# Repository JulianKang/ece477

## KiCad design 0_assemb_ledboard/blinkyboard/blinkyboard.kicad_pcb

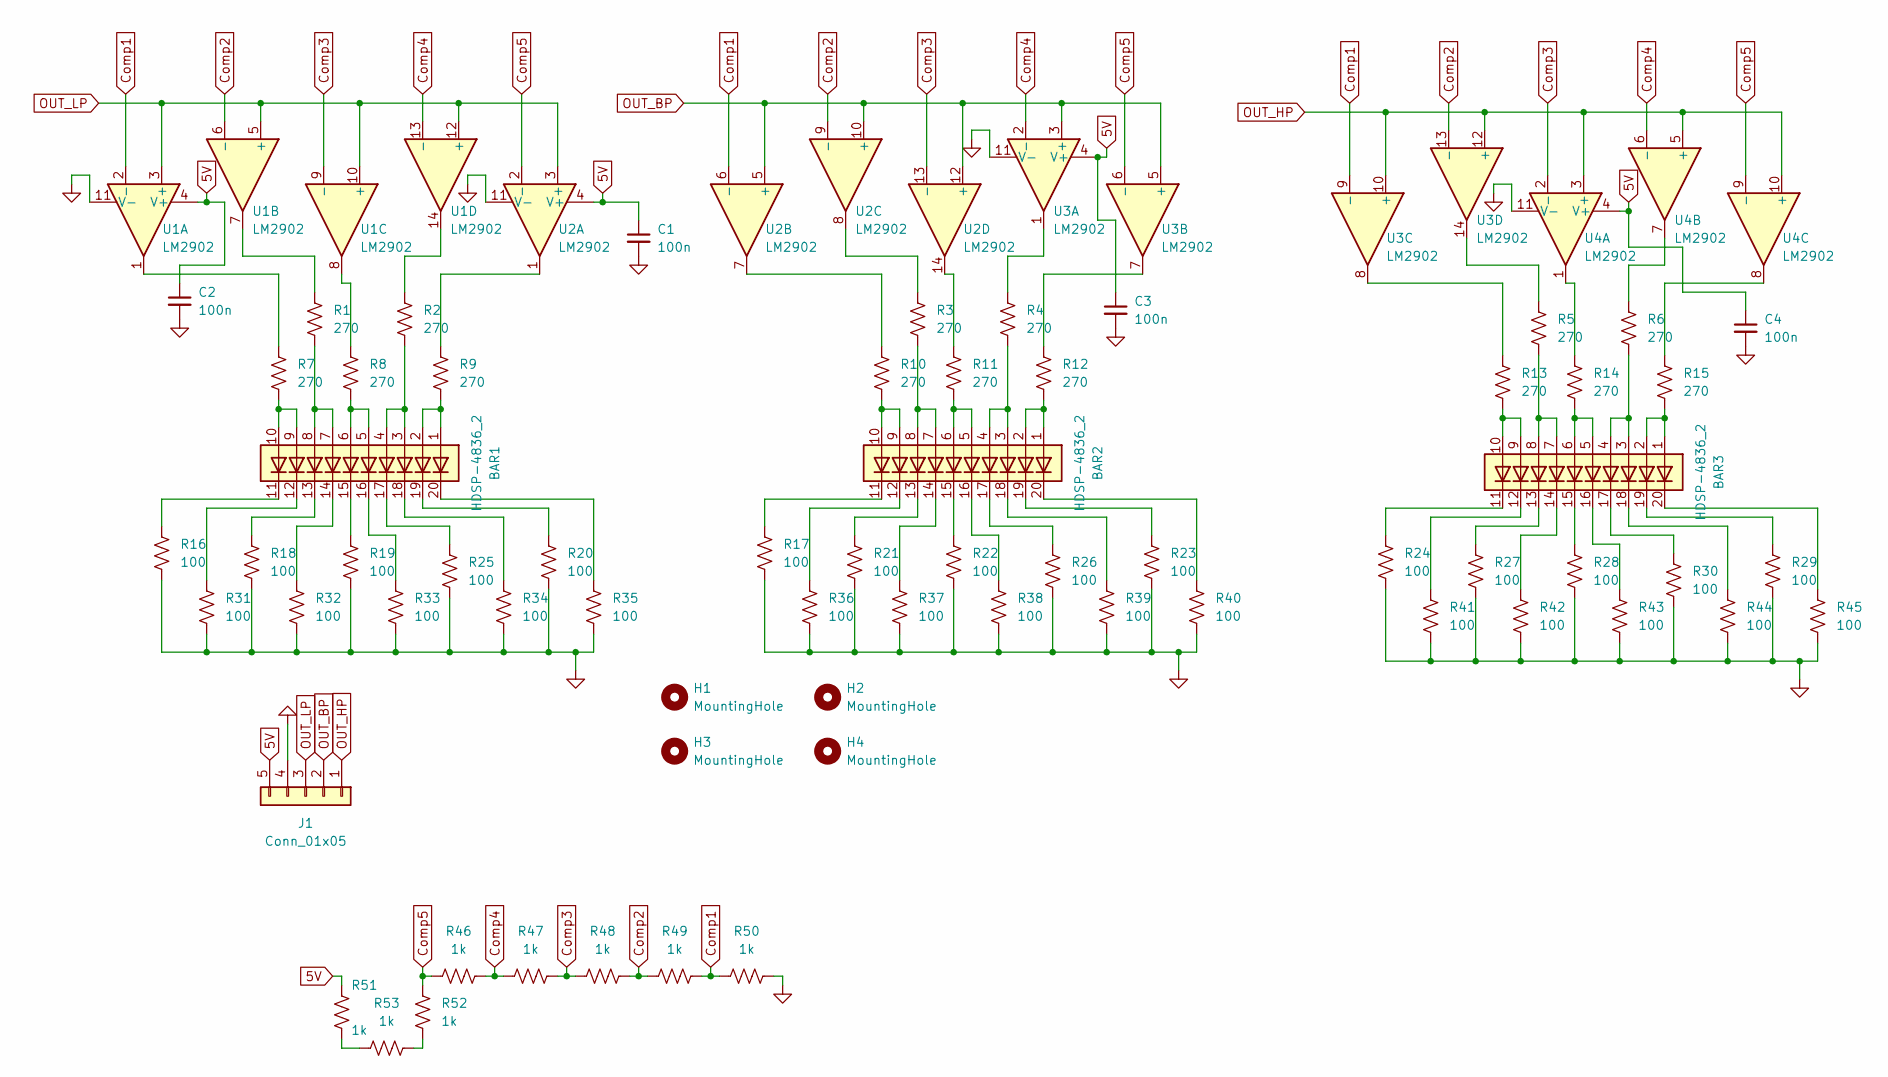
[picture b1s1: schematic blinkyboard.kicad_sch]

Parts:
BAR1, BAR2, BAR3: HDSP-4836_2; HDSP-4836
C1, C2, C3, C4: 100n; C_0805_2012Metric
H1, H2, H3, H4: MountingHole; MountingHole_3.2mm_M3_DIN965
J1: Conn_01x05; PinHeader_1x05_P2.54mm_Vertical
R1, R2, R3, R4, R5, R6, R7, R8, R9, R10, R11, R12, R13, R14, R15: 270; R_0805_2012Metric_Pad1.20x1.40mm_HandSolder
R16, R17, R18, R19, R20, R21, R22, R23, R24, R25, R26, R27, R28, R29, R30, R31, R32, R33, R34, R35, R36, R37, R38, R39, R40, R41, R42, R43, R44, R45: 100; R_0805_2012Metric_Pad1.20x1.40mm_HandSolder
R46, R47, R48, R49, R50, R51, R52, R53: 1k; R_0805_2012Metric_Pad1.20x1.40mm_HandSolder
U1, U2, U3, U4: LM2902; DIP-14_W7.62mm

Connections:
5V: C1.1, C2.1, C3.1, C4.1, J1.5, R51.2, U1.4 (V+), U2.4 (V+), U3.4 (V+), U4.4 (V+)
Comp1: R49.1, R50.2, U1.2 (-), U2.6 (-), U3.9 (-)
Comp2: R48.1, R49.2, U1.6 (-), U2.9 (-), U3.13 (-)
Comp3: R47.1, R48.2, U1.9 (-), U2.13 (-), U4.2 (-)
Comp4: R46.1, R47.2, U1.13 (-), U3.2 (-), U4.6 (-)
Comp5: R46.2, R52.2, U2.2 (-), U3.6 (-), U4.9 (-)
GND: C1.2, C2.2, C3.2, C4.2, J1.4, R16.1, R17.1, R18.1, R19.1, R20.1, R21.1, R22.1, R23.1, R24.1, R25.1, R26.1, R27.1, R28.1, R29.1, R30.1, R31.1, R32.1, R33.1, R34.1, R35.1, R36.1, R37.1, R38.1, R39.1, R40.1, R41.1, R42.1, R43.1, R44.1, R45.1, R50.1, U1.11 (V-), U2.11 (V-), U3.11 (V-), U4.11 (V-)
unnamed: BAR1.1 (A), BAR1.2 (A), R9.1
unnamed: BAR1.3 (A), BAR1.4 (A), R2.1
unnamed: BAR1.5 (A), BAR1.6 (A), R8.1
unnamed: BAR1.7 (A), BAR1.8 (A), R1.1
unnamed: BAR1.9 (A), BAR1.10 (A), R7.1
unnamed: BAR1.11 (K), R16.2
unnamed: BAR1.12 (K), R31.2
unnamed: BAR1.13 (K), R18.2
unnamed: BAR1.14 (K), R32.2
unnamed: BAR1.15 (K), R19.2
unnamed: BAR1.16 (K), R33.2
unnamed: BAR1.17 (K), R25.2
unnamed: BAR1.18 (K), R34.2
unnamed: BAR1.19 (K), R20.2
unnamed: BAR1.20 (K), R35.2
unnamed: BAR2.1 (A), BAR2.2 (A), R12.1
unnamed: BAR2.3 (A), BAR2.4 (A), R4.1
unnamed: BAR2.5 (A), BAR2.6 (A), R11.1
unnamed: BAR2.7 (A), BAR2.8 (A), R3.1
unnamed: BAR2.9 (A), BAR2.10 (A), R10.1
unnamed: BAR2.11 (K), R17.2
unnamed: BAR2.12 (K), R36.2
unnamed: BAR2.13 (K), R21.2
unnamed: BAR2.14 (K), R37.2
unnamed: BAR2.15 (K), R22.2
unnamed: BAR2.16 (K), R38.2
unnamed: BAR2.17 (K), R26.2
unnamed: BAR2.18 (K), R39.2
unnamed: BAR2.19 (K), R23.2
unnamed: BAR2.20 (K), R40.2
unnamed: BAR3.1 (A), BAR3.2 (A), R15.1
unnamed: BAR3.3 (A), BAR3.4 (A), R6.1
unnamed: BAR3.5 (A), BAR3.6 (A), R14.1
unnamed: BAR3.7 (A), BAR3.8 (A), R5.1
unnamed: BAR3.9 (A), BAR3.10 (A), R13.1
unnamed: BAR3.11 (K), R24.2
unnamed: BAR3.12 (K), R41.2
unnamed: BAR3.13 (K), R27.2
unnamed: BAR3.14 (K), R42.2
unnamed: BAR3.15 (K), R28.2
unnamed: BAR3.16 (K), R43.2
unnamed: BAR3.17 (K), R30.2
unnamed: BAR3.18 (K), R44.2
unnamed: BAR3.19 (K), R29.2
unnamed: BAR3.20 (K), R45.2
unnamed: R1.2, U1.7
unnamed: R2.2, U1.14
unnamed: R3.2, U2.8
unnamed: R4.2, U3.1
unnamed: R5.2, U3.14
unnamed: R6.2, U4.7
unnamed: R7.2, U1.1
unnamed: R8.2, U1.8
unnamed: R9.2, U2.1
unnamed: R10.2, U2.7
unnamed: R11.2, U2.14
unnamed: R12.2, U3.7
unnamed: R13.2, U3.8
unnamed: R14.2, U4.1
unnamed: R15.2, U4.8
unnamed: R51.1, R53.2
unnamed: R52.1, R53.1
OUT_BP: J1.2, U2.5 (+), U2.10 (+), U2.12 (+), U3.3 (+), U3.5 (+)
OUT_HP: J1.1, U3.10 (+), U3.12 (+), U4.3 (+), U4.5 (+), U4.10 (+)
OUT_LP: J1.3, U1.3 (+), U1.5 (+), U1.10 (+), U1.12 (+), U2.3 (+)

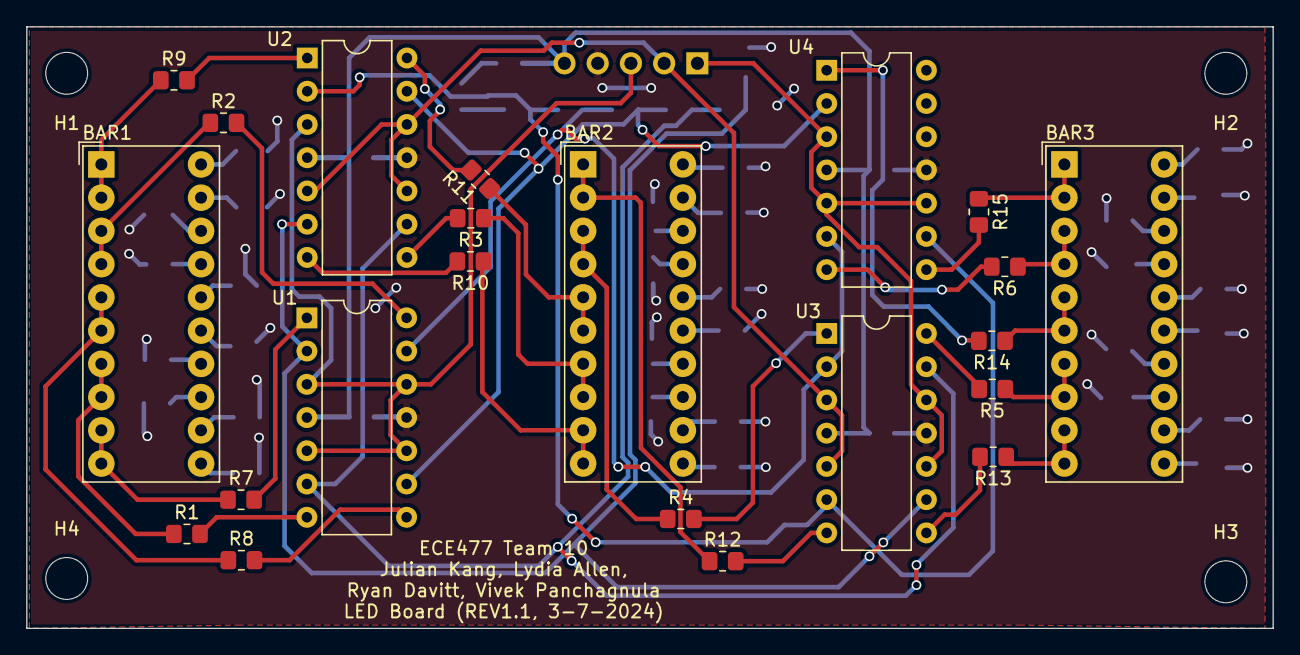
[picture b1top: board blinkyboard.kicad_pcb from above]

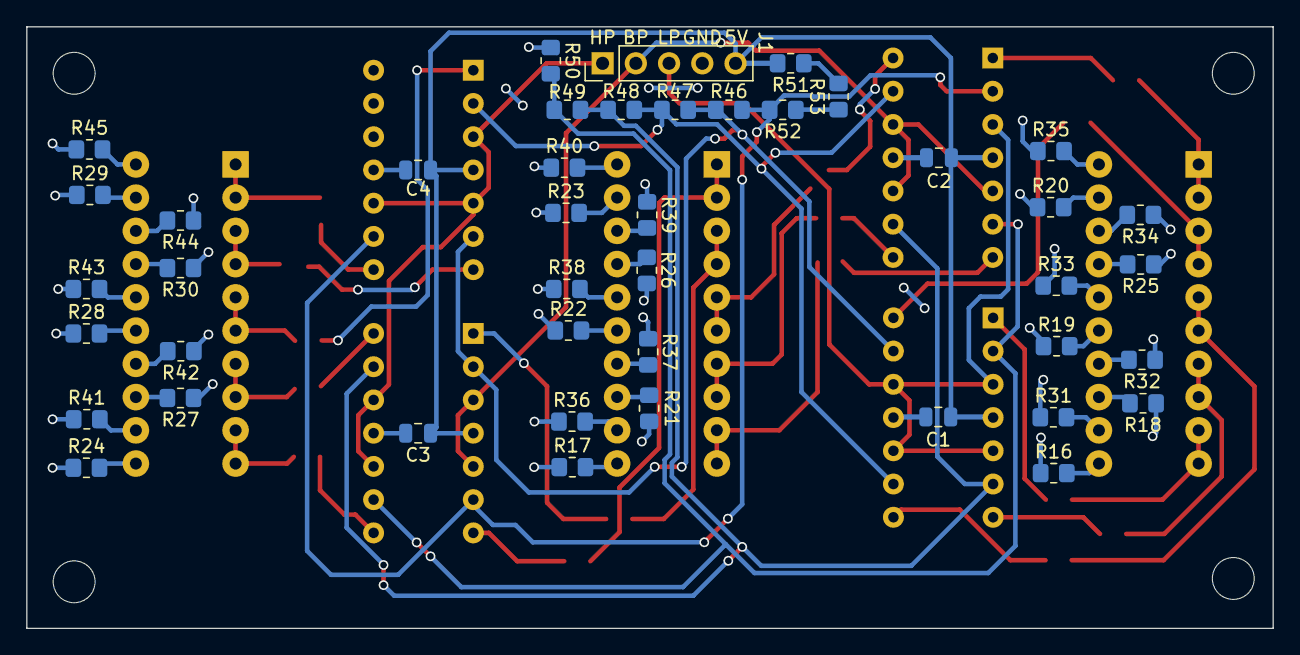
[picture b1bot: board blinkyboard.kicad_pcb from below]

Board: 2 copper layers, 95.2 x 46.0 mm, 69 parts (43 on the bottom side), 72 nets.

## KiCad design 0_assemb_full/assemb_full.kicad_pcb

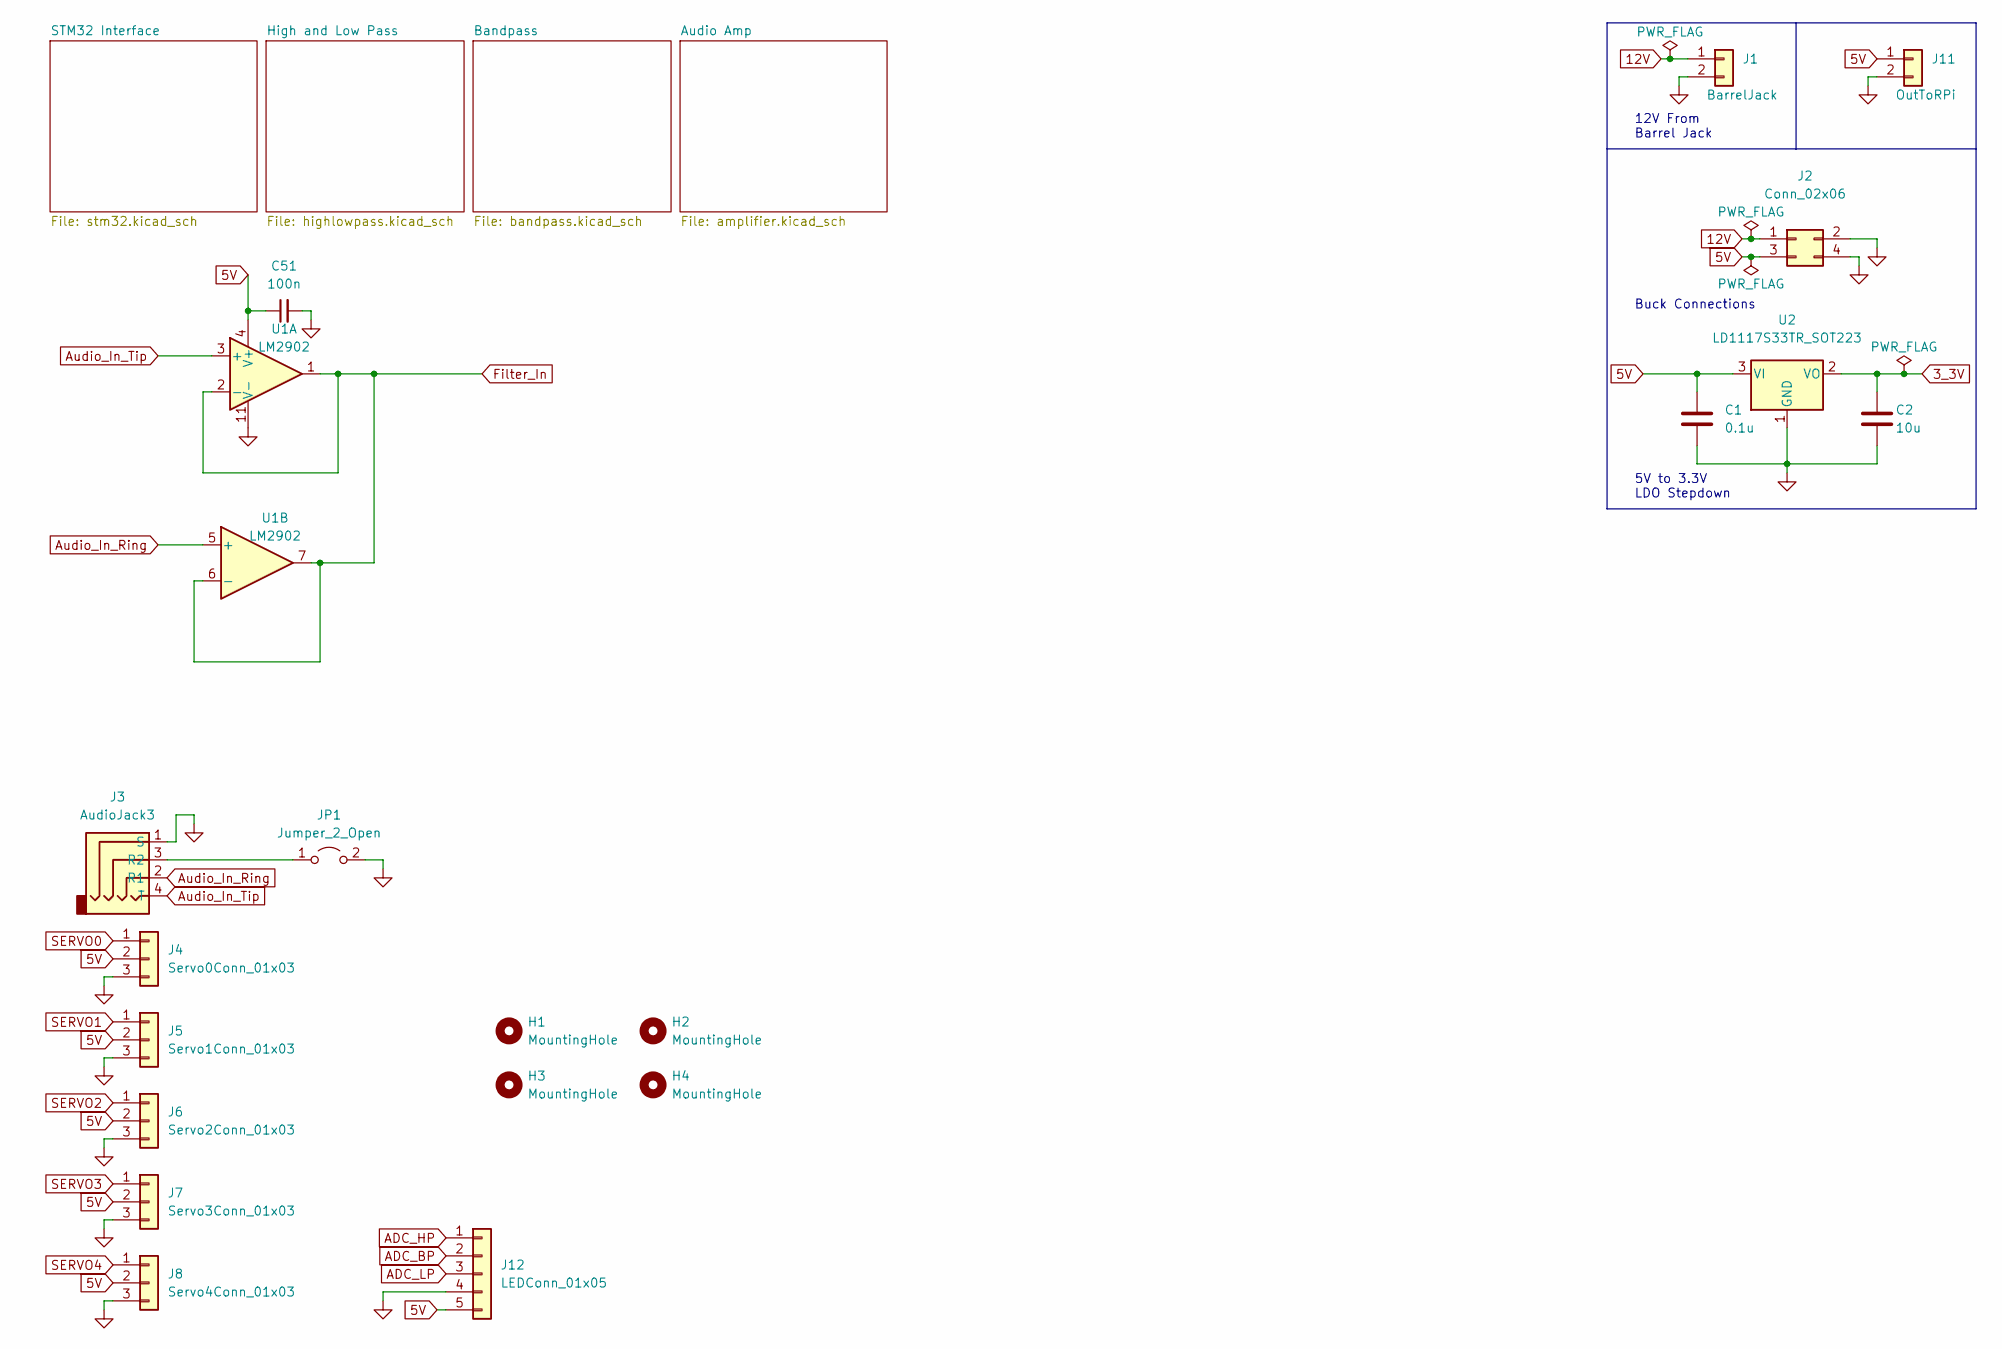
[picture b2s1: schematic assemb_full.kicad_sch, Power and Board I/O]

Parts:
C1: 0.1u; C_0805_2012Metric_Pad1.18x1.45mm_HandSolder
C2: 10u; C_0805_2012Metric_Pad1.18x1.45mm_HandSolder
C51: 100n; C_0805_2012Metric_Pad1.18x1.45mm_HandSolder
H1, H2, H3, H4: MountingHole; MountingHole_3.2mm_M3
J1: BarrelJack; BarrelJack_GCT_DCJ200-10-A_Horizontal
J2: Conn_02x06; PinHeader_2x02_P2.54mm_Vertical
J3: AudioJack3; PinSocket_1x04_P2.54mm_Vertical
J4: Servo0Conn_01x03; PinHeader_1x03_P2.54mm_Vertical
J5: Servo1Conn_01x03; PinHeader_1x03_P2.54mm_Vertical
J6: Servo2Conn_01x03; PinHeader_1x03_P2.54mm_Vertical
J7: Servo3Conn_01x03; PinHeader_1x03_P2.54mm_Vertical
J8: Servo4Conn_01x03; PinHeader_1x03_P2.54mm_Vertical
J11: OutToRPi; PinHeader_1x02_P2.54mm_Vertical
J12: LEDConn_01x05; PinHeader_1x05_P2.54mm_Vertical
JP1: Jumper_2_Open; SolderJumper-2_P1.3mm_Open_Pad1.0x1.5mm
U1: LM2902; DIP-14_W7.62mm
U2: LD1117S33TR_SOT223; SOT-223-3_TabPin2

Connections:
3_3V: C2.1, U2.2 (VO); also elsewhere on the board
5V: C1.1, C51.1, J2.3, J4.2, J5.2, J6.2, J7.2, J8.2, J11.1, J12.5, U1.4 (V+), U2.3 (VI); also elsewhere on the board
12V: J1.1, J2.1; also elsewhere on the board
ADC_BP: J12.2; also elsewhere on the board
ADC_HP: J12.1; also elsewhere on the board
ADC_LP: J12.3; also elsewhere on the board
Audio_In_Ring: J3.2 (R1), U1.5 (+); also elsewhere on the board
Audio_In_Tip: J3.4 (T), U1.3 (+); also elsewhere on the board
Filter_In: U1.1, U1.2 (-), U1.6 (-), U1.7; also elsewhere on the board
GND: C1.2, C2.2, C51.2, J1.2, J2.2, J2.4, J3.1 (S), J4.3, J5.3, J6.3, J7.3, J8.3, J11.2, J12.4, JP1.2 (B), U1.11 (V-), U2.1 (GND); also elsewhere on the board
unnamed: J3.3 (R2), JP1.1 (A)
SERVO0: J4.1; also elsewhere on the board
SERVO1: J5.1; also elsewhere on the board
SERVO2: J6.1; also elsewhere on the board
SERVO3: J7.1; also elsewhere on the board
SERVO4: J8.1; also elsewhere on the board

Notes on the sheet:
12V From Barrel Jack
5V to 3.3V LDO Stepdown
Buck Connections

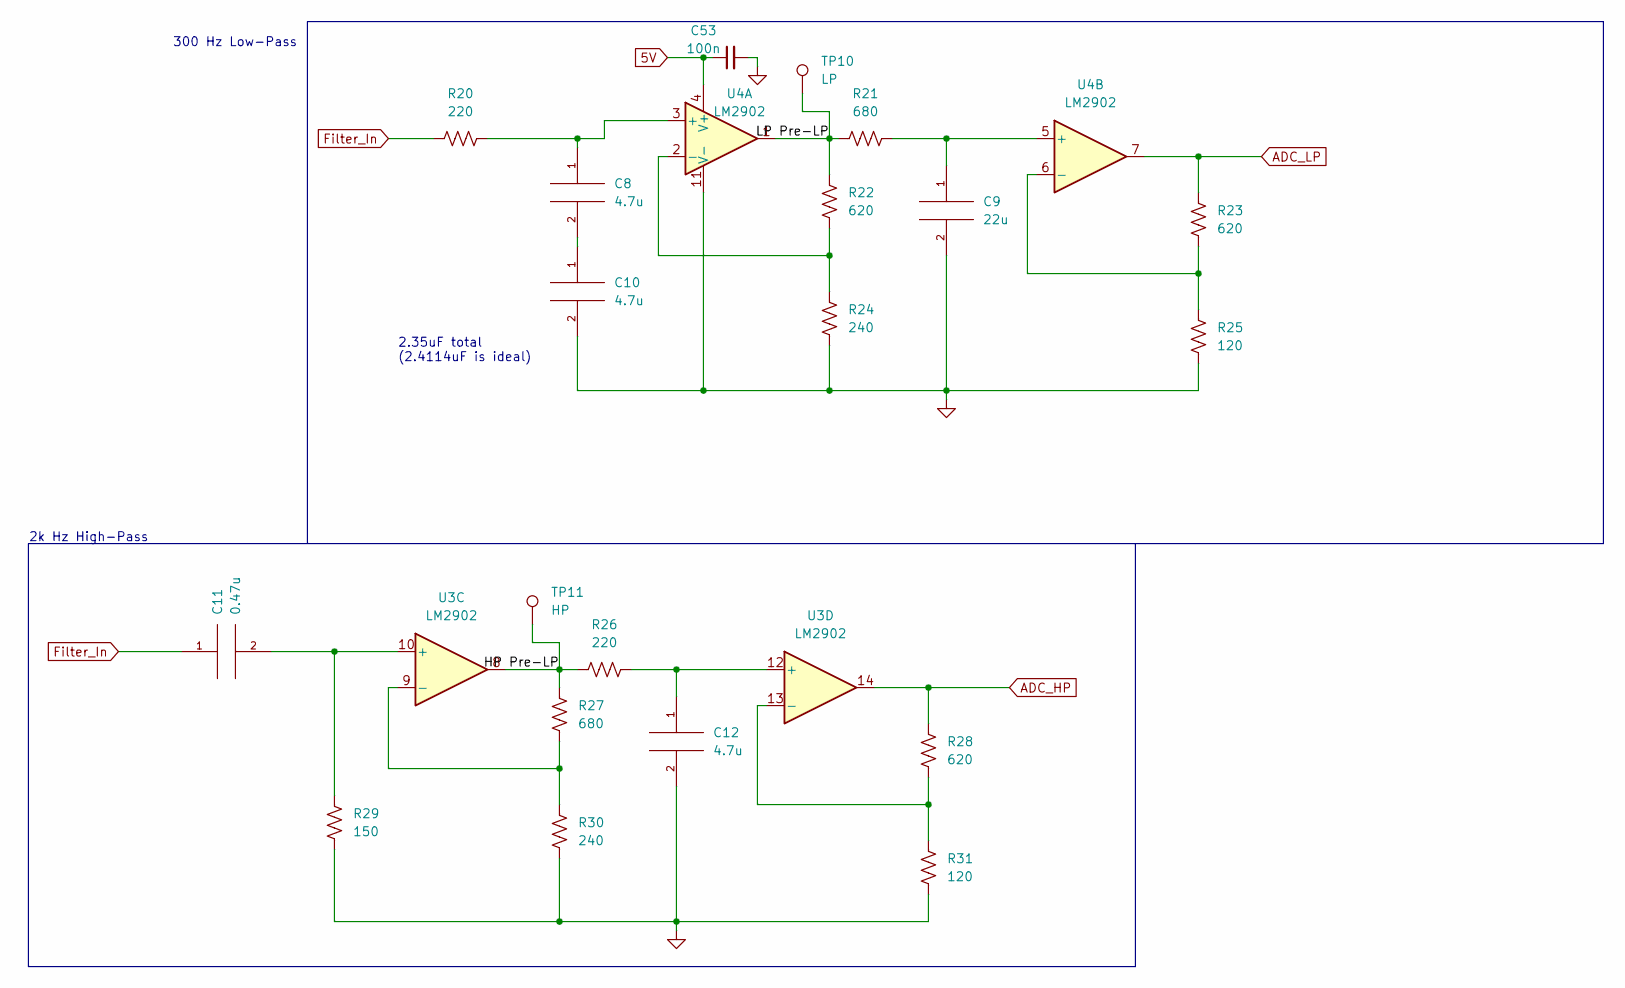
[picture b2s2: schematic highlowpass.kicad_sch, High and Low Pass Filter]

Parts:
C8, C10, C12: 4.7u; C_Rect_L26.5mm_W7.0mm_P22.50mm_MKS4
C9: 22u; CP_Elec_5x5.8
C11: 0.47u; C_Rect_L7.2mm_W3.5mm_P5.00mm_FKS2_FKP2_MKS2_MKP2
C53: 100n; C_0805_2012Metric_Pad1.18x1.45mm_HandSolder
R20, R26: 220; R_0805_2012Metric_Pad1.20x1.40mm_HandSolder
R21, R27: 680; R_0805_2012Metric_Pad1.20x1.40mm_HandSolder
R22, R23, R28: 620; R_0805_2012Metric_Pad1.20x1.40mm_HandSolder
R24, R30: 240; R_0805_2012Metric_Pad1.20x1.40mm_HandSolder
R25, R31: 120; R_0805_2012Metric_Pad1.20x1.40mm_HandSolder
R29: 150; R_0805_2012Metric_Pad1.20x1.40mm_HandSolder
TP10: LP; TestPoint_THTPad_2.0x2.0mm_Drill1.0mm
TP11: HP; TestPoint_THTPad_2.0x2.0mm_Drill1.0mm
U3, U4: LM2902; DIP-14_W7.62mm

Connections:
5V: C53.1, U4.4 (V+); also elsewhere on the board
/High and Low Pass/HP Pre-LP: R26.1, R27.2, TP11.1, U3.8
/High and Low Pass/LP Pre-LP: R21.1, R22.2, TP10.1, U4.1
ADC_HP: R28.2, U3.14; also elsewhere on the board
ADC_LP: R23.2, U4.7; also elsewhere on the board
Filter_In: C11.1, R20.1; also elsewhere on the board
GND: C9.2, C10.2, C12.2, C53.2, R24.1, R25.1, R29.1, R30.1, R31.1, U4.11 (V-); also elsewhere on the board
unnamed: C8.1, R20.2, U4.3 (+)
unnamed: C9.1, R21.2, U4.5 (+)
unnamed: C8.2, C10.1
unnamed: C11.2, R29.2, U3.10 (+)
unnamed: C12.1, R26.2, U3.12 (+)
unnamed: R22.1, R24.2, U4.2 (-)
unnamed: R23.1, R25.2, U4.6 (-)
unnamed: R27.1, R30.2, U3.9 (-)
unnamed: R28.1, R31.2, U3.13 (-)

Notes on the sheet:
2k Hz High-Pass
2.35uF total (2.4114uF is ideal)
300 Hz Low-Pass

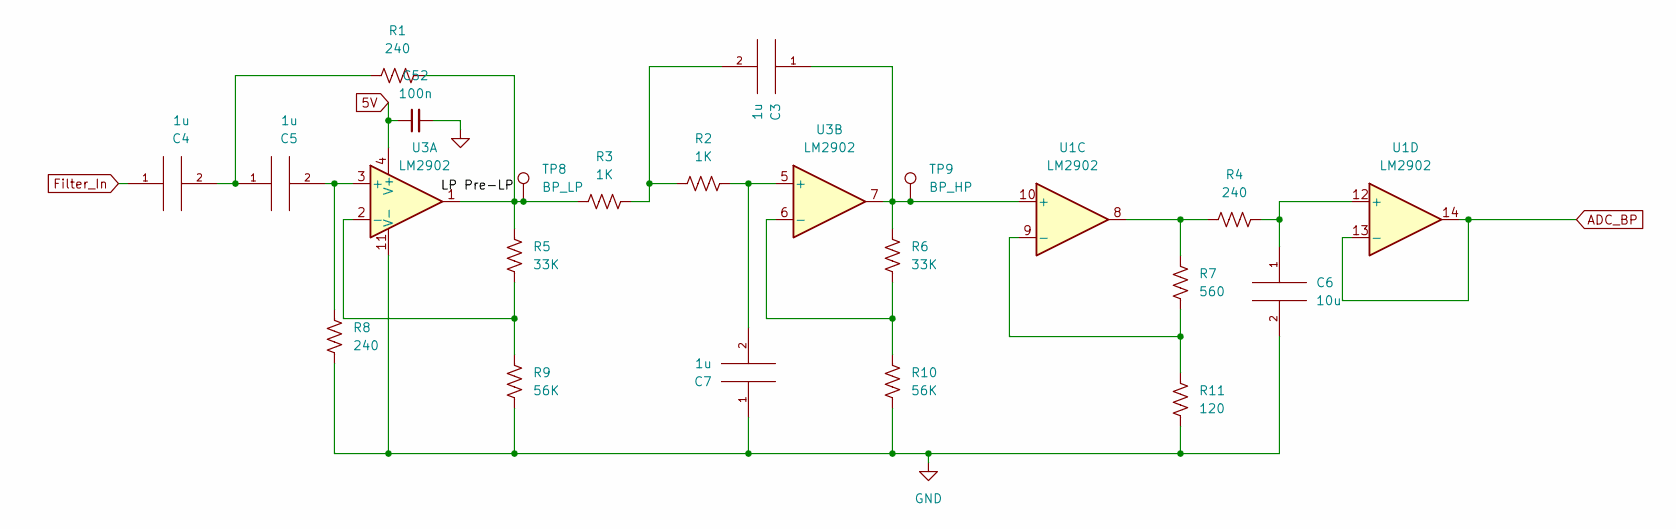
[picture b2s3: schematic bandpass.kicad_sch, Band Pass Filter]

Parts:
C3, C4, C5, C7: 1u; C_Rect_L7.0mm_W4.5mm_P5.00mm
C6: 10u; CP_Elec_5x5.4
C52: 100n; C_0805_2012Metric_Pad1.18x1.45mm_HandSolder
R1, R4, R8: 240; R_0805_2012Metric_Pad1.20x1.40mm_HandSolder
R2, R3: 1K; R_0805_2012Metric_Pad1.20x1.40mm_HandSolder
R5, R6: 33K; R_0805_2012Metric_Pad1.20x1.40mm_HandSolder
R7: 560; R_0805_2012Metric_Pad1.20x1.40mm_HandSolder
R9, R10: 56K; R_0805_2012Metric_Pad1.20x1.40mm_HandSolder
R11: 120; R_0805_2012Metric_Pad1.20x1.40mm_HandSolder
TP8: BP_LP; TestPoint_THTPad_2.0x2.0mm_Drill1.0mm
TP9: BP_HP; TestPoint_THTPad_2.0x2.0mm_Drill1.0mm
U1, U3: LM2902; DIP-14_W7.62mm

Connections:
5V: C52.1, U3.4 (V+); also elsewhere on the board
/Bandpass/LP Pre-LP: R1.1, R3.2, R5.2, TP8.1, U3.1
ADC_BP: U1.13 (-), U1.14; also elsewhere on the board
Filter_In: C4.1; also elsewhere on the board
GND: C6.2, C7.1, C52.2, R8.1, R9.1, R10.1, R11.1, U3.11 (V-); also elsewhere on the board
unnamed: C3.1, R6.2, TP9.1, U1.10 (+), U3.7
unnamed: C3.2, R2.2, R3.1
unnamed: C4.2, C5.1, R1.2
unnamed: C5.2, R8.2, U3.3 (+)
unnamed: C6.1, R4.2, U1.12 (+)
unnamed: C7.2, R2.1, U3.5 (+)
unnamed: R4.1, R7.2, U1.8
unnamed: R5.1, R9.2, U3.2 (-)
unnamed: R6.1, R10.2, U3.6 (-)
unnamed: R7.1, R11.2, U1.9 (-)

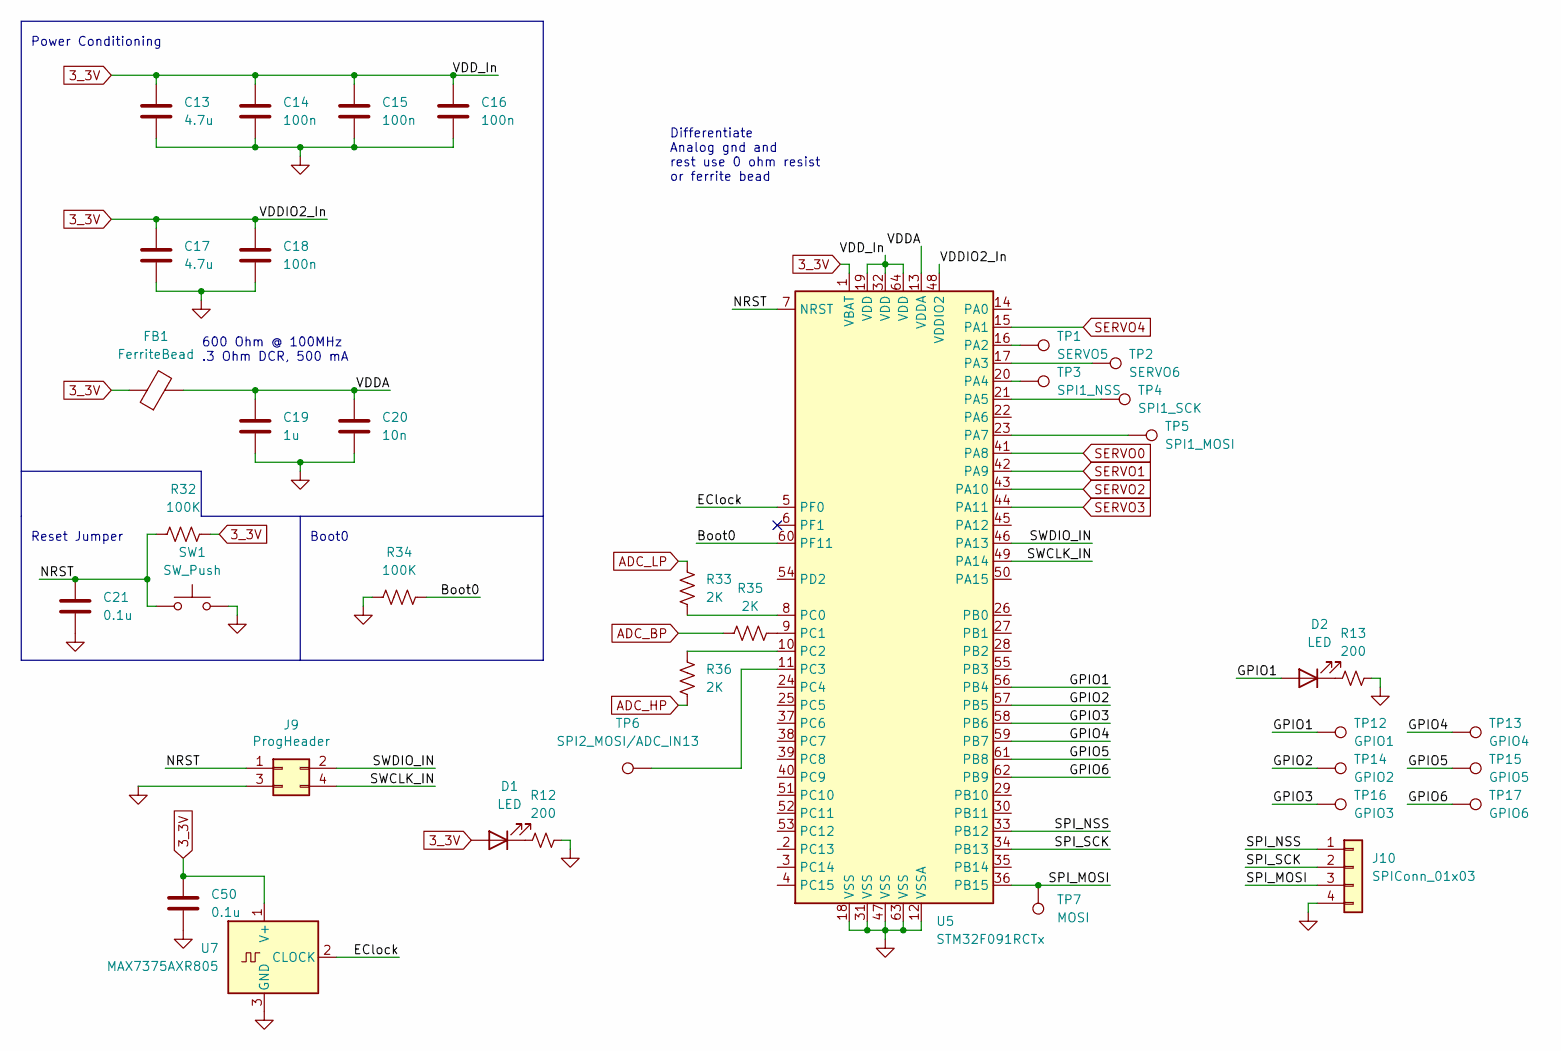
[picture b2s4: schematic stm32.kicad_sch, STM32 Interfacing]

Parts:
C13, C17: 4.7u; C_0805_2012Metric_Pad1.18x1.45mm_HandSolder
C14, C15, C16, C18: 100n; C_0805_2012Metric_Pad1.18x1.45mm_HandSolder
C19: 1u; C_0805_2012Metric_Pad1.18x1.45mm_HandSolder
C20: 10n; C_0805_2012Metric_Pad1.18x1.45mm_HandSolder
C21, C50: 0.1u; C_0805_2012Metric_Pad1.18x1.45mm_HandSolder
D1, D2: LED; LED_0805_2012Metric_Pad1.15x1.40mm_HandSolder
FB1: FerriteBead; R_0805_2012Metric_Pad1.20x1.40mm_HandSolder
J9: ProgHeader; PinHeader_2x02_P2.54mm_Vertical
J10: SPIConn_01x03; PinHeader_1x04_P2.54mm_Vertical
R12, R13: 200; R_0805_2012Metric_Pad1.20x1.40mm_HandSolder
R32, R34: 100K; R_0805_2012Metric_Pad1.20x1.40mm_HandSolder
R33, R35, R36: 2K; R_0805_2012Metric_Pad1.20x1.40mm_HandSolder
SW1: SW_Push; SW_PUSH-12mm_Wuerth-430476085716
TP1: SERVO5; TestPoint_THTPad_1.5x1.5mm_Drill0.7mm
TP2: SERVO6; TestPoint_THTPad_1.5x1.5mm_Drill0.7mm
TP3: SPI1_NSS; TestPoint_THTPad_1.5x1.5mm_Drill0.7mm
TP4: SPI1_SCK; TestPoint_THTPad_1.5x1.5mm_Drill0.7mm
TP5: SPI1_MOSI; TestPoint_THTPad_1.5x1.5mm_Drill0.7mm
TP6: SPI2_MOSI/ADC_IN13; TestPoint_THTPad_1.5x1.5mm_Drill0.7mm
TP7: MOSI; TestPoint_THTPad_2.0x2.0mm_Drill1.0mm
TP12: GPIO1; TestPoint_THTPad_2.0x2.0mm_Drill1.0mm
TP13: GPIO4; TestPoint_THTPad_2.0x2.0mm_Drill1.0mm
TP14: GPIO2; TestPoint_THTPad_2.0x2.0mm_Drill1.0mm
TP15: GPIO5; TestPoint_THTPad_2.0x2.0mm_Drill1.0mm
TP16: GPIO3; TestPoint_THTPad_2.0x2.0mm_Drill1.0mm
TP17: GPIO6; TestPoint_THTPad_2.0x2.0mm_Drill1.0mm
U5: STM32F091RCTx; LQFP-64_10x10mm_P0.5mm
U7: MAX7375AXR805; SOT-323_SC-70

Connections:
3_3V: C13.1, C14.1, C15.1, C16.1, C17.1, C18.1, C50.1, D1.2 (A), FB1.1, R32.2, U5.1 (VBAT), U5.19 (VDD), U5.32 (VDD), U5.48 (VDDIO2), U5.64 (VDD), U7.1 (V+); also elsewhere on the board
/STM32 Interface/Boot0: R34.2, U5.60 (PF11)
/STM32 Interface/EClock: U5.5 (PF0), U7.2 (CLOCK)
/STM32 Interface/GPIO1: D2.2 (A), TP12.1, U5.56 (PB4)
/STM32 Interface/GPIO2: TP14.1, U5.57 (PB5)
/STM32 Interface/GPIO3: TP16.1, U5.58 (PB6)
/STM32 Interface/GPIO4: TP13.1, U5.59 (PB7)
/STM32 Interface/GPIO5: TP15.1, U5.61 (PB8)
/STM32 Interface/GPIO6: TP17.1, U5.62 (PB9)
/STM32 Interface/NRST: C21.1, J9.1, R32.1, SW1.1, U5.7 (NRST)
/STM32 Interface/SPI_MOSI: J10.3, TP7.1, U5.36 (PB15)
/STM32 Interface/SPI_NSS: J10.1, U5.33 (PB12)
/STM32 Interface/SPI_SCK: J10.2, U5.34 (PB13)
/STM32 Interface/SWCLK_IN: J9.4, U5.49 (PA14)
/STM32 Interface/SWDIO_IN: J9.2, U5.46 (PA13)
/STM32 Interface/VDDA: C19.1, C20.1, FB1.2, U5.13 (VDDA)
ADC_BP: R35.1; also elsewhere on the board
ADC_HP: R36.1; also elsewhere on the board
ADC_LP: R33.2; also elsewhere on the board
GND: C13.2, C14.2, C15.2, C16.2, C17.2, C18.2, C19.2, C20.2, C21.2, C50.2, J9.3, J10.4, R12.2, R13.2, R34.1, SW1.2, U5.12 (VSSA), U5.18 (VSS), U5.31 (VSS), U5.47 (VSS), U5.63 (VSS), U7.3 (GND); also elsewhere on the board
unnamed: D1.1 (K), R12.1
unnamed: D2.1 (K), R13.1
unnamed: R33.1, U5.8 (PC0)
unnamed: R35.2, U5.9 (PC1)
unnamed: R36.2, U5.10 (PC2)
unnamed: TP1.1, U5.16 (PA2)
unnamed: TP2.1, U5.17 (PA3)
unnamed: TP3.1, U5.20 (PA4)
unnamed: TP4.1, U5.21 (PA5)
unnamed: TP5.1, U5.23 (PA7)
unnamed: TP6.1, U5.11 (PC3)
SERVO0: U5.41 (PA8); also elsewhere on the board
SERVO1: U5.42 (PA9); also elsewhere on the board
SERVO2: U5.43 (PA10); also elsewhere on the board
SERVO3: U5.44 (PA11); also elsewhere on the board
SERVO4: U5.15 (PA1); also elsewhere on the board

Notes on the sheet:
Differentiate Analog gnd and rest use 0 ohm resist or ferrite bead
600 Ohm @ 100MHz .3 Ohm DCR, 500 mA
Boot0
Power Conditioning
Reset Jumper

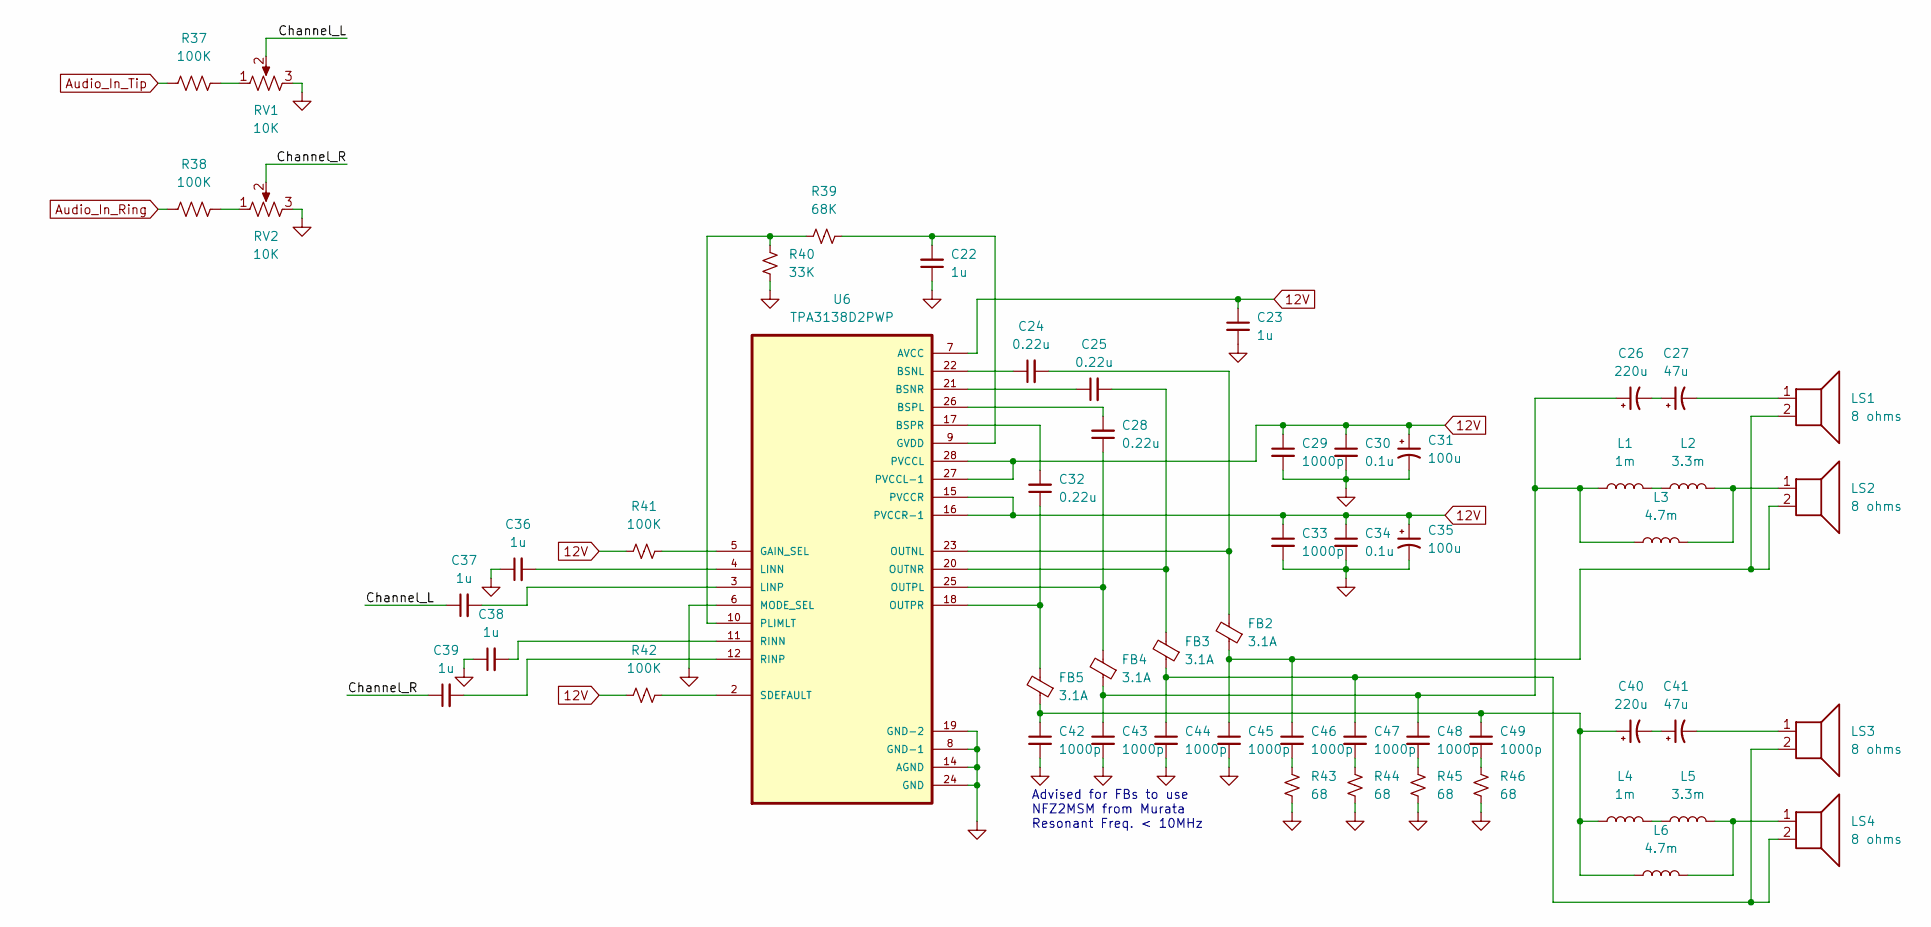
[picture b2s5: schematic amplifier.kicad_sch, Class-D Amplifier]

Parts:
C22, C23, C36, C37, C38, C39: 1u; C_0805_2012Metric_Pad1.18x1.45mm_HandSolder
C24, C25, C28, C32: 0.22u; C_0805_2012Metric_Pad1.18x1.45mm_HandSolder
C26, C40: 220u; CP_Radial_D6.3mm_P2.50mm
C27, C41: 47u; CP_Radial_D6.3mm_P2.50mm
C29, C33, C42, C43, C44, C45, C46, C47, C48, C49: 1000p; C_0805_2012Metric_Pad1.18x1.45mm_HandSolder
C30, C34: 0.1u; C_0805_2012Metric_Pad1.18x1.45mm_HandSolder
C31, C35: 100u; CP_Radial_D5.0mm_P2.50mm
FB2, FB3, FB4, FB5: 3.1A; BEADC2016X100N
L1, L4: 1m; L_Radial_D9.5mm_P5.00mm_Fastron_07HVP
L2, L5: 3.3m; L_Radial_D9.5mm_P5.00mm_Fastron_07HVP
L3, L6: 4.7m; L_Radial_D9.5mm_P5.00mm_Fastron_07HVP
LS1, LS2, LS3, LS4: 8 ohms; SolderWire-2sqmm_1x02_P7.8mm_D2mm_OD3.9mm
R37, R38, R41, R42: 100K; R_0805_2012Metric_Pad1.20x1.40mm_HandSolder
R39: 68K; R_0805_2012Metric_Pad1.20x1.40mm_HandSolder
R40: 33K; R_0805_2012Metric_Pad1.20x1.40mm_HandSolder
R43, R44, R45, R46: 68; R_0805_2012Metric_Pad1.20x1.40mm_HandSolder
RV1, RV2: 10K; Potentiometer_Vishay_148-149_Single_Vertical
U6: TPA3138D2PWP; IC_TPS61196PWPRQ1

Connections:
12V: C23.1, C29.1, C30.1, C31.1, C33.1, C34.1, C35.1, R41.1, R42.1, U6.7 (AVCC), U6.15 (PVCCR), U6.16 (PVCCR-1), U6.27 (PVCCL-1), U6.28 (PVCCL); also elsewhere on the board
/Audio Amp/Channel_L: C37.1, RV1.2
/Audio Amp/Channel_R: C39.1, RV2.2
Audio_In_Ring: R38.1; also elsewhere on the board
Audio_In_Tip: R37.1; also elsewhere on the board
GND: C22.1, C23.2, C29.2, C30.2, C31.2, C33.2, C34.2, C35.2, C36.1, C38.1, C42.2, C43.2, C44.2, C45.2, R40.1, R43.1, R44.1, R45.1, R46.1, RV1.3, RV2.3, U6.6 (MODE_SEL), U6.8 (GND-1), U6.14 (AGND), U6.19 (GND-2), U6.24 (GND); also elsewhere on the board
unnamed: C22.2, R39.2, U6.9 (GVDD)
unnamed: C24.1, U6.22 (BSNL)
unnamed: C24.2, FB2.2, U6.23 (OUTNL)
unnamed: C25.1, U6.21 (BSNR)
unnamed: C25.2, FB3.2, U6.20 (OUTNR)
unnamed: C26.1, C43.1, C48.1, FB4.1, L1.1, L3.1
unnamed: C26.2, C27.1
unnamed: C27.2, LS1.1
unnamed: C28.1, FB4.2, U6.25 (OUTPL)
unnamed: C28.2, U6.26 (BSPL)
unnamed: C32.1, FB5.2, U6.18 (OUTPR)
unnamed: C32.2, U6.17 (BSPR)
unnamed: C36.2, U6.4 (LINN)
unnamed: C37.2, U6.3 (LINP)
unnamed: C38.2, U6.11 (RINN)
unnamed: C39.2, U6.12 (RINP)
unnamed: C40.1, C42.1, C49.1, FB5.1, L4.1, L6.1
unnamed: C40.2, C41.1
unnamed: C41.2, LS3.1
unnamed: C44.1, C47.1, FB3.1, LS3.2, LS4.2
unnamed: C45.1, C46.1, FB2.1, LS1.2, LS2.2
unnamed: C46.2, R43.2
unnamed: C47.2, R44.2
unnamed: C48.2, R45.2
unnamed: C49.2, R46.2
unnamed: L1.2, L2.1
unnamed: L2.2, L3.2, LS2.1
unnamed: L4.2, L5.1
unnamed: L5.2, L6.2, LS4.1
unnamed: R37.2, RV1.1
unnamed: R38.2, RV2.1
unnamed: R39.1, R40.2, U6.10 (PLIMLT)
unnamed: R41.2, U6.5 (GAIN_SEL)
unnamed: R42.2, U6.2 (SDEFAULT)

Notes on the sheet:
Advised for FBs to use NFZ2MSM from Murata Resonant Freq. < 10MHz
